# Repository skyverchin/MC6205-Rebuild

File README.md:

# MC6205-Rebuild
Restoration of soviet era plasma display

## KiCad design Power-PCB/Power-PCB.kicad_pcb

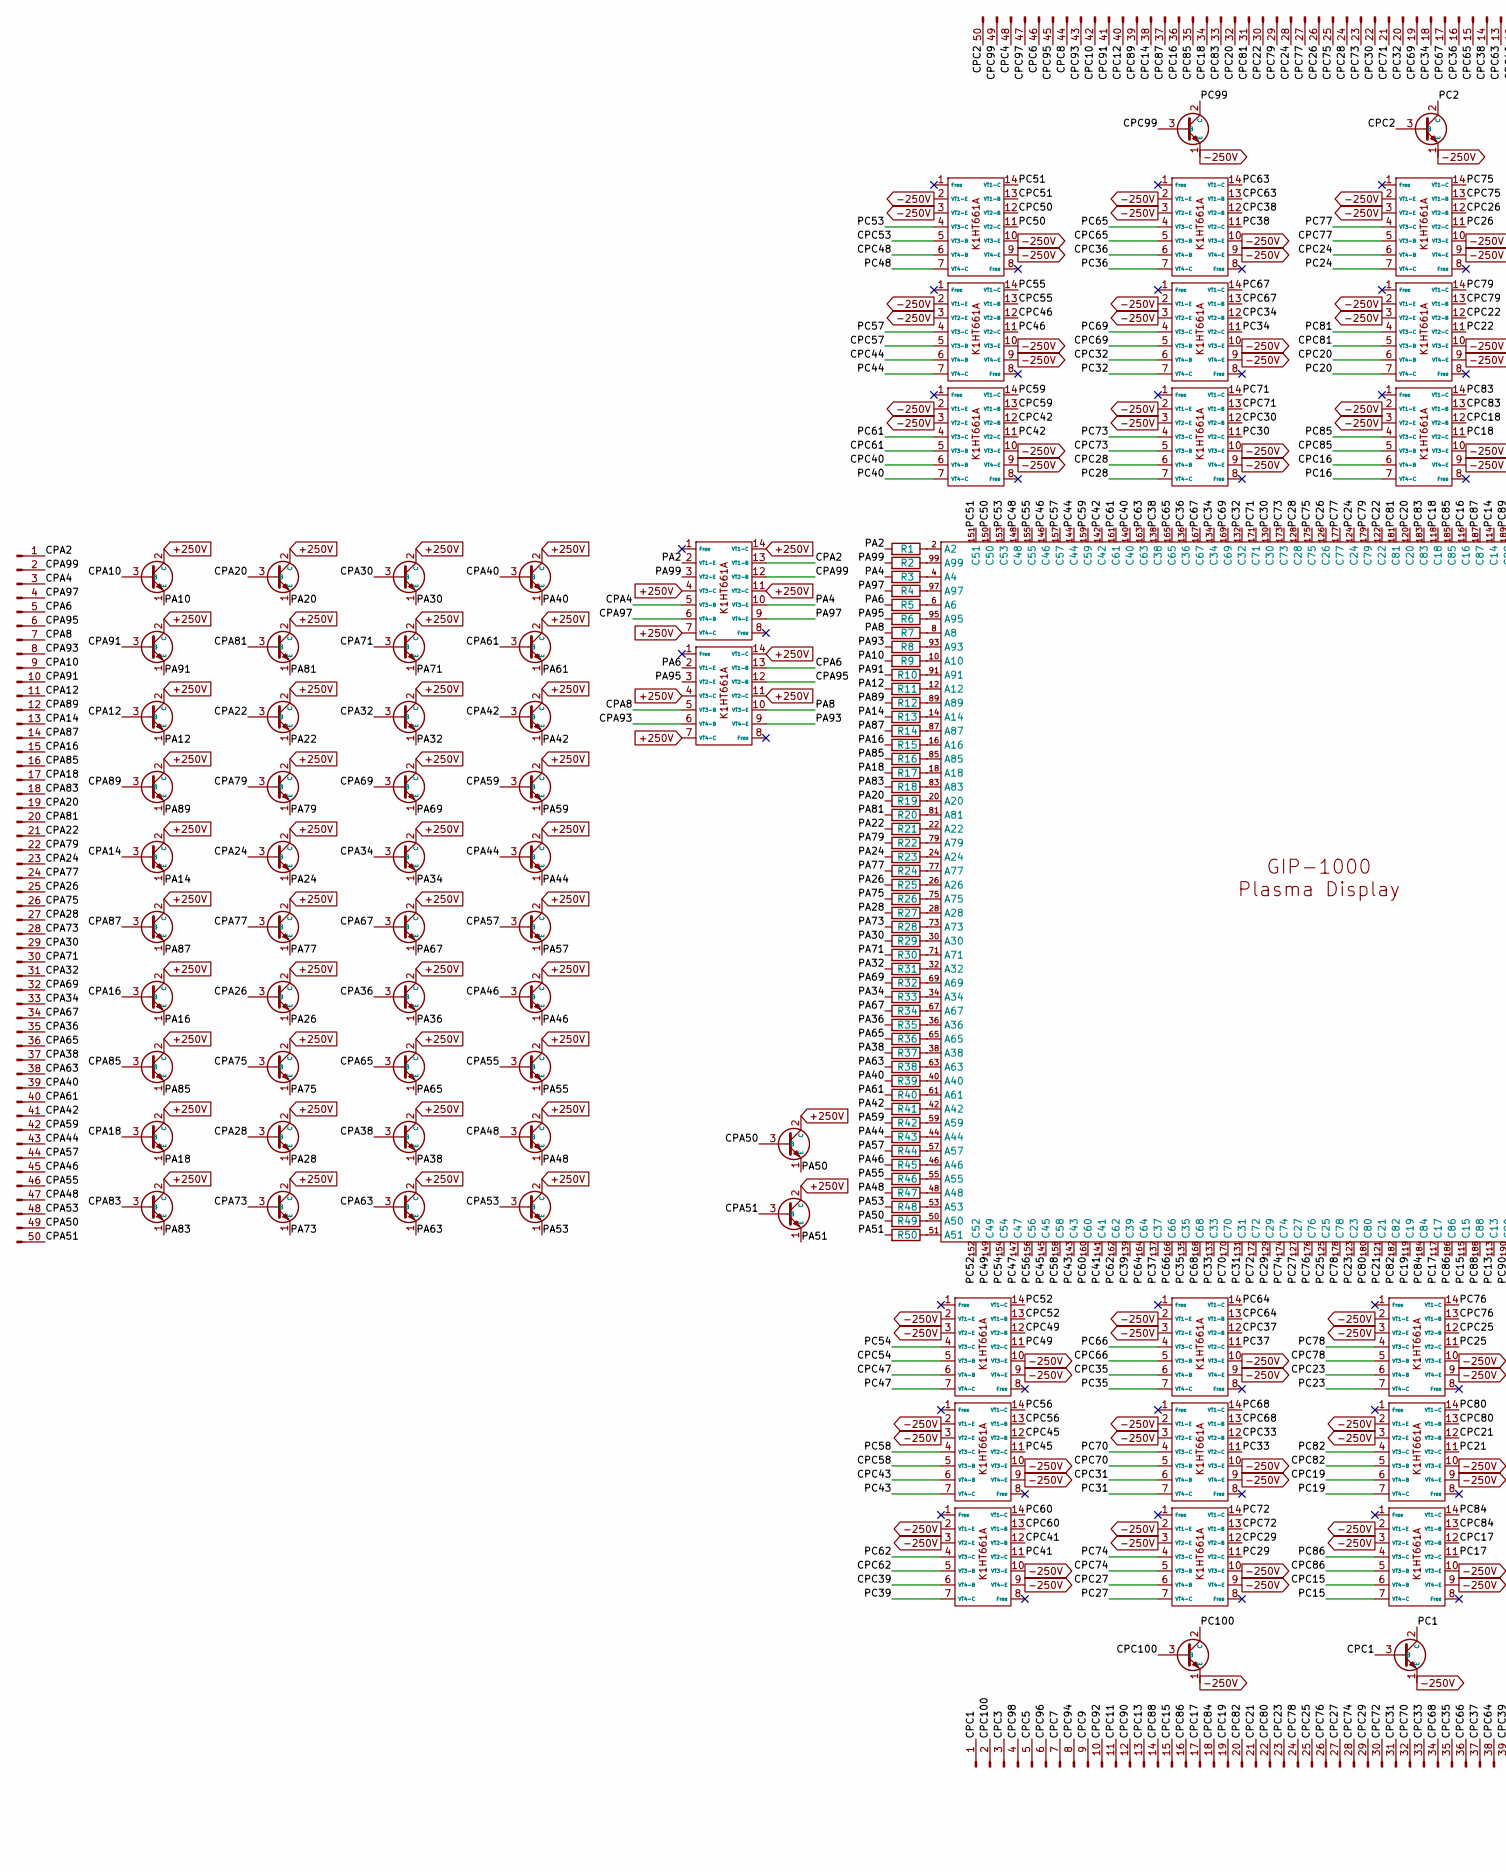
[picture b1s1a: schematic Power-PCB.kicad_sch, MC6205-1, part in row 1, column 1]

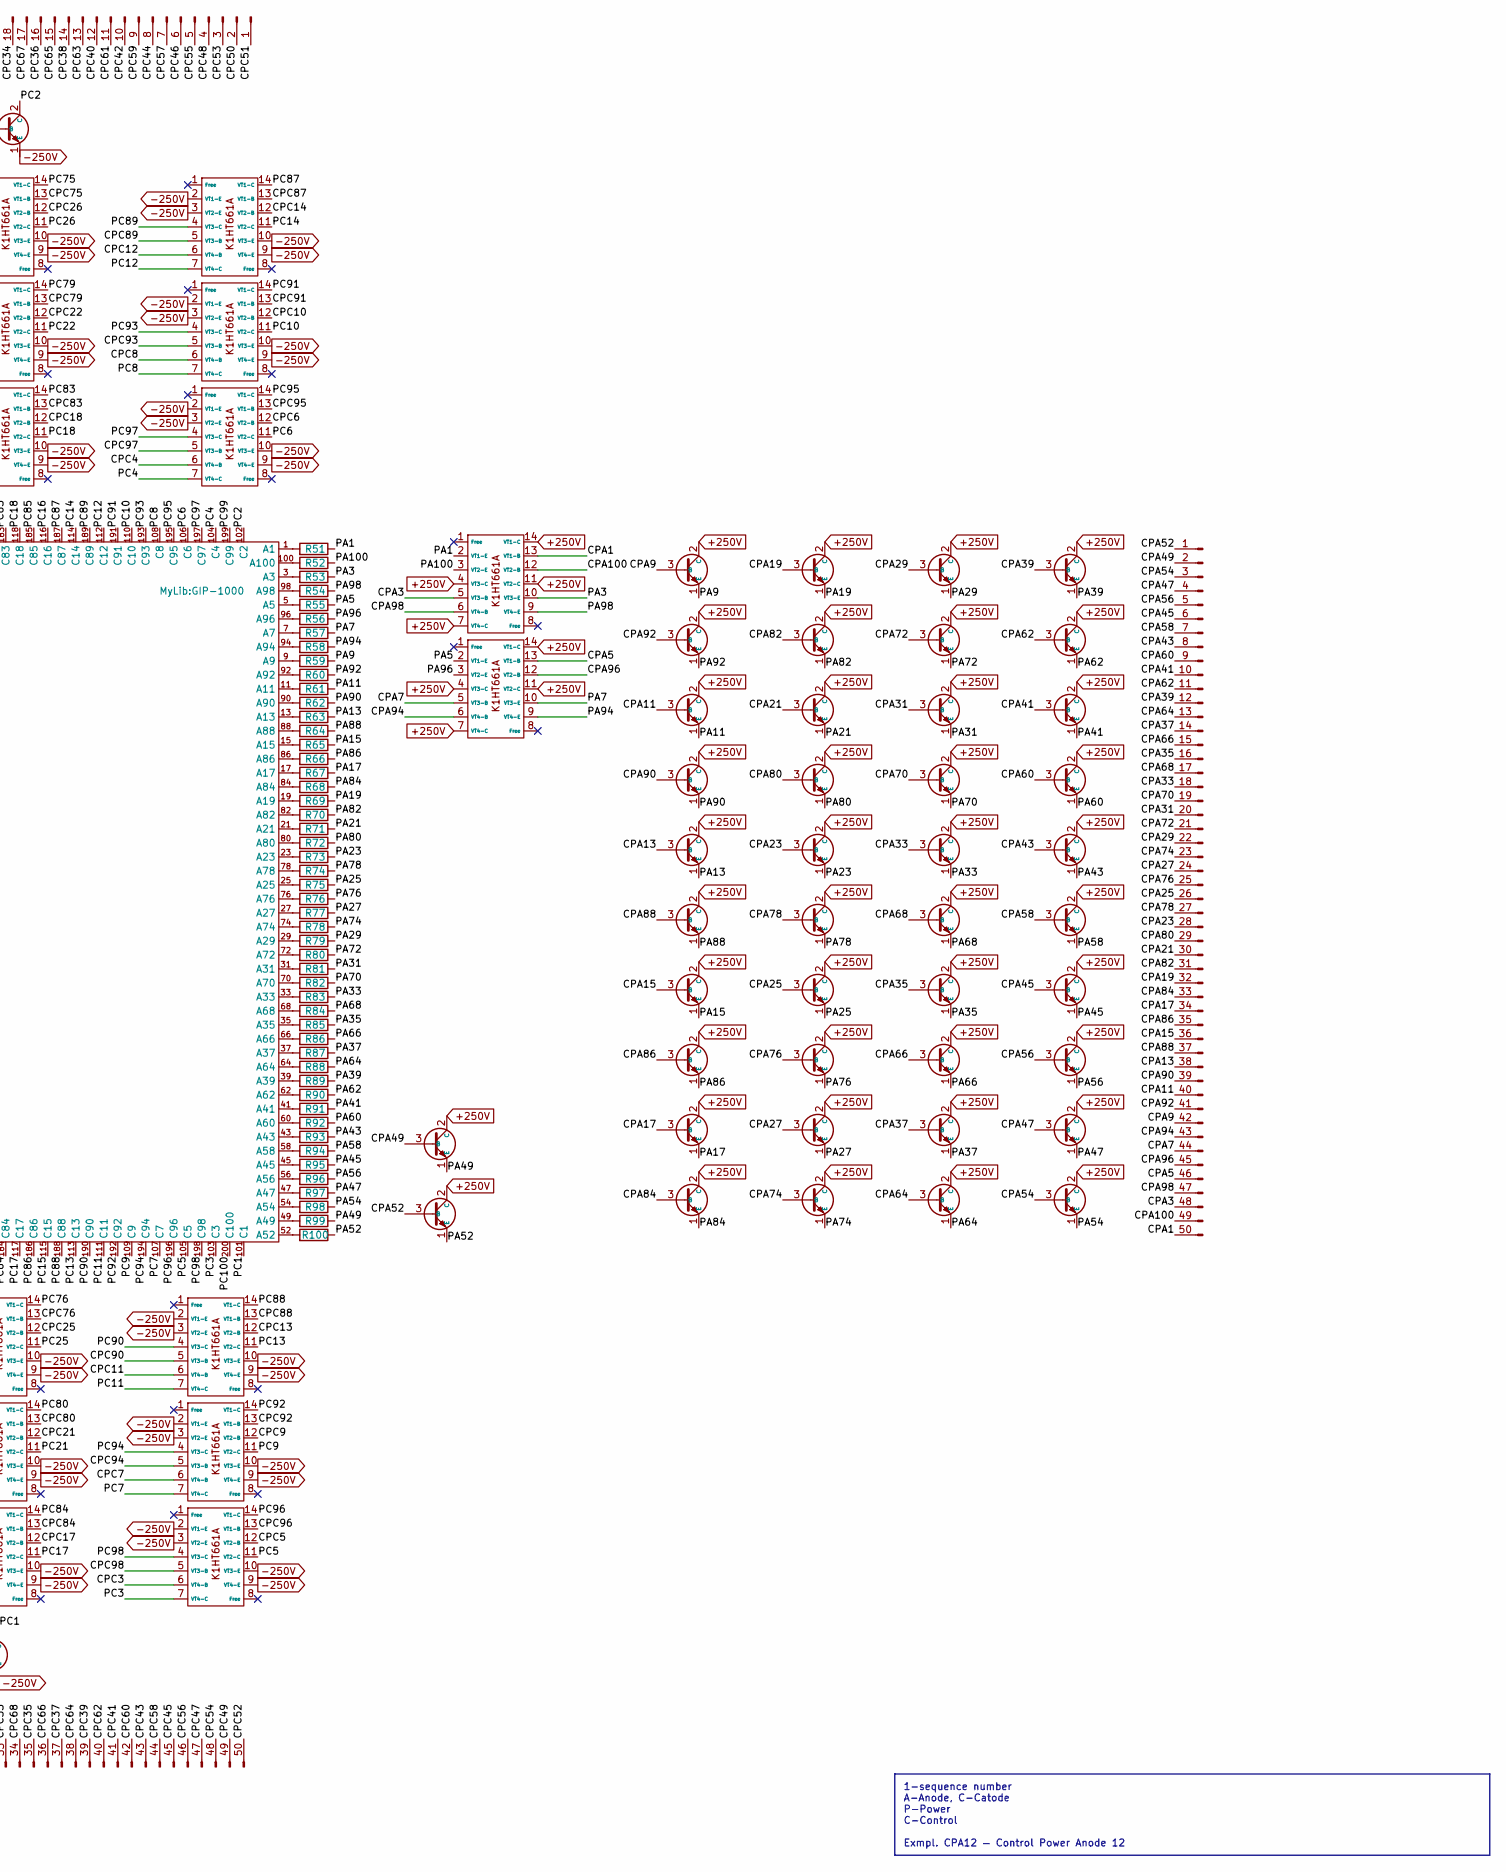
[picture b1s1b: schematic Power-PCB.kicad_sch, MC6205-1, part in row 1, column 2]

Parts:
J1, J2, J3, J4: Conn_01x50_Pin; Molex_54132-5033_1x50-1MP_P0.5mm_Horizontal
R1, R2, R3, R4, R5, R6, R7, R8, R9, R10, R11, R12, R13, R14, R15, R16, R17, R18, R19, R20, R21, R22, R23, R24, R25, R26, R27, R28, R29, R30, R31, R32, R33, R34, R35, R36, R37, R38, R39, R40, R41, R42, R43, R44, R45, R46, R47, R48, R49, R50, R51, R52, R53, R54, R55, R56, R57, R58, R59, R60, R61, R62, R63, R64, R65, R66, R67, R68, R69, R70, R71, R72, R73, R74, R75, R76, R77, R78, R79, R80, R81, R82, R83, R84, R85, R86, R87, R88, R89, R90, R91, R92, R93, R94, R95, R96, R97, R98, R99, R100: R_5K1; 5K1
U1, U2, U3, U4, U5, U6, U7, U8, U9, U10, U11, U12, U13, U14, U15, U16, U17, U18, U19, U20, U21, U22, U23, U24, U25, U26, U27, U28, U29, U30, U31, U32, U33, U34, U35, U36, U37, U38, U39, U40, U43, U44, U51, U52, U60, U67, U74, U75, U78, U79, U80, U81, U82, U83, U84, U85, U86, U87, U88, U89, U90, U91, U92, U93, U94, U95, U96, U97, U98, U99, U100, U101, U102, U103, U104, U105, U106, U107, U108, U109, U110, U111, U112, U113, U114, U115, U116, U117: BF422-FTPRNT
U41, U42, U45, U46, U47, U48, U49, U50, U53, U54, U55, U56, U57, U58, U61, U62, U63, U64, U65, U66, U68, U69, U70, U71, U72, U73, U76, U77: K1HT661A-FTPRNT
U59: GIP-1000

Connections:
+250V: U1.2 (C), U2.2 (C), U3.2 (C), U4.2 (C), U5.2 (C), U6.2 (C), U7.2 (C), U8.2 (C), U9.2 (C), U10.2 (C), U11.2 (C), U12.2 (C), U13.2 (C), U14.2 (C), U15.2 (C), U16.2 (C), U17.2 (C), U18.2 (C), U19.2 (C), U20.2 (C), U21.2 (C), U22.2 (C), U23.2 (C), U24.2 (C), U25.2 (C), U26.2 (C), U27.2 (C), U28.2 (C), U29.2 (C), U30.2 (C), U31.2 (C), U32.2 (C), U33.2 (C), U34.2 (C), U35.2 (C), U36.2 (C), U37.2 (C), U38.2 (C), U39.2 (C), U40.2 (C), U41.4 (VT3-C), U41.7 (VT4-C), U41.11 (VT2-C), U41.14 (VT1-C), U42.4 (VT3-C), U42.7 (VT4-C), U42.11 (VT2-C), U42.14 (VT1-C), U43.2 (C), U44.2 (C), U74.2 (C), U75.2 (C), U76.4 (VT3-C), U76.7 (VT4-C), U76.11 (VT2-C), U76.14 (VT1-C), U77.4 (VT3-C), U77.7 (VT4-C), U77.11 (VT2-C), U77.14 (VT1-C), U78.2 (C), U79.2 (C), U80.2 (C), U81.2 (C), U82.2 (C), U83.2 (C), U84.2 (C), U85.2 (C), U86.2 (C), U87.2 (C), U88.2 (C), U89.2 (C), U90.2 (C), U91.2 (C), U92.2 (C), U93.2 (C), U94.2 (C), U95.2 (C), U96.2 (C), U97.2 (C), U98.2 (C), U99.2 (C), U100.2 (C), U101.2 (C), U102.2 (C), U103.2 (C), U104.2 (C), U105.2 (C), U106.2 (C), U107.2 (C), U108.2 (C), U109.2 (C), U110.2 (C), U111.2 (C), U112.2 (C), U113.2 (C), U114.2 (C), U115.2 (C), U116.2 (C), U117.2 (C)
-250V: U45.2 (VT1-E), U45.3 (VT2-E), U45.9 (VT4-E), U45.10 (VT3-E), U46.2 (VT1-E), U46.3 (VT2-E), U46.9 (VT4-E), U46.10 (VT3-E), U47.2 (VT1-E), U47.3 (VT2-E), U47.9 (VT4-E), U47.10 (VT3-E), U48.2 (VT1-E), U48.3 (VT2-E), U48.9 (VT4-E), U48.10 (VT3-E), U49.2 (VT1-E), U49.3 (VT2-E), U49.9 (VT4-E), U49.10 (VT3-E), U50.2 (VT1-E), U50.3 (VT2-E), U50.9 (VT4-E), U50.10 (VT3-E), U51.1 (E), U52.1 (E), U53.2 (VT1-E), U53.3 (VT2-E), U53.9 (VT4-E), U53.10 (VT3-E), U54.2 (VT1-E), U54.3 (VT2-E), U54.9 (VT4-E), U54.10 (VT3-E), U55.2 (VT1-E), U55.3 (VT2-E), U55.9 (VT4-E), U55.10 (VT3-E), U56.2 (VT1-E), U56.3 (VT2-E), U56.9 (VT4-E), U56.10 (VT3-E), U57.2 (VT1-E), U57.3 (VT2-E), U57.9 (VT4-E), U57.10 (VT3-E), U58.2 (VT1-E), U58.3 (VT2-E), U58.9 (VT4-E), U58.10 (VT3-E), U60.1 (E), U61.2 (VT1-E), U61.3 (VT2-E), U61.9 (VT4-E), U61.10 (VT3-E), U62.2 (VT1-E), U62.3 (VT2-E), U62.9 (VT4-E), U62.10 (VT3-E), U63.2 (VT1-E), U63.3 (VT2-E), U63.9 (VT4-E), U63.10 (VT3-E), U64.2 (VT1-E), U64.3 (VT2-E), U64.9 (VT4-E), U64.10 (VT3-E), U65.2 (VT1-E), U65.3 (VT2-E), U65.9 (VT4-E), U65.10 (VT3-E), U66.2 (VT1-E), U66.3 (VT2-E), U66.9 (VT4-E), U66.10 (VT3-E), U67.1 (E), U68.2 (VT1-E), U68.3 (VT2-E), U68.9 (VT4-E), U68.10 (VT3-E), U69.2 (VT1-E), U69.3 (VT2-E), U69.9 (VT4-E), U69.10 (VT3-E), U70.2 (VT1-E), U70.3 (VT2-E), U70.9 (VT4-E), U70.10 (VT3-E), U71.2 (VT1-E), U71.3 (VT2-E), U71.9 (VT4-E), U71.10 (VT3-E), U72.2 (VT1-E), U72.3 (VT2-E), U72.9 (VT4-E), U72.10 (VT3-E), U73.2 (VT1-E), U73.3 (VT2-E), U73.9 (VT4-E), U73.10 (VT3-E)
/CPA1: J4.50, U76.13 (VT1-B)
/CPA3: J4.48, U76.5 (VT3-B)
/CPA5: J4.46, U77.13 (VT1-B)
/CPA7: J4.44, U77.5 (VT3-B)
/CPA9: J4.42, U78.3 (B)
/CPA11: J4.40, U80.3 (B)
/CPA13: J4.38, U82.3 (B)
/CPA15: J4.36, U84.3 (B)
/CPA17: J4.34, U86.3 (B)
/CPA19: J4.32, U88.3 (B)
/CPA21: J4.30, U90.3 (B)
/CPA23: J4.28, U92.3 (B)
/CPA25: J4.26, U94.3 (B)
/CPA27: J4.24, U96.3 (B)
/CPA29: J4.22, U98.3 (B)
/CPA31: J4.20, U100.3 (B)
/CPA33: J4.18, U102.3 (B)
/CPA35: J4.16, U104.3 (B)
/CPA37: J4.14, U106.3 (B)
/CPA39: J4.12, U108.3 (B)
/CPA41: J4.10, U110.3 (B)
/CPA43: J4.8, U112.3 (B)
/CPA45: J4.6, U114.3 (B)
/CPA47: J4.4, U116.3 (B)
/CPA49: J4.2, U74.3 (B)
/CPA52: J4.1, U75.3 (B)
/CPA54: J4.3, U117.3 (B)
/CPA56: J4.5, U115.3 (B)
/CPA58: J4.7, U113.3 (B)
/CPA60: J4.9, U111.3 (B)
/CPA62: J4.11, U109.3 (B)
/CPA64: J4.13, U107.3 (B)
/CPA66: J4.15, U105.3 (B)
/CPA68: J4.17, U103.3 (B)
/CPA70: J4.19, U101.3 (B)
/CPA72: J4.21, U99.3 (B)
/CPA74: J4.23, U97.3 (B)
/CPA76: J4.25, U95.3 (B)
/CPA78: J4.27, U93.3 (B)
/CPA80: J4.29, U91.3 (B)
/CPA82: J4.31, U89.3 (B)
/CPA84: J4.33, U87.3 (B)
/CPA86: J4.35, U85.3 (B)
/CPA88: J4.37, U83.3 (B)
/CPA90: J4.39, U81.3 (B)
/CPA92: J4.41, U79.3 (B)
/CPA94: J4.43, U77.6 (VT4-B)
/CPA96: J4.45, U77.12 (VT2-B)
/CPA98: J4.47, U76.6 (VT4-B)
/CPA100: J4.49, U76.12 (VT2-B)
/CPC1: J2.1, U60.3 (B)
/CPC2: J3.50, U67.3 (B)
/CPC3: J2.3, U70.6 (VT4-B)
/CPC4: J3.48, U73.6 (VT4-B)
/CPC5: J2.5, U70.12 (VT2-B)
/CPC6: J3.46, U73.12 (VT2-B)
/CPC7: J2.7, U69.6 (VT4-B)
/CPC8: J3.44, U72.6 (VT4-B)
/CPC9: J2.9, U69.12 (VT2-B)
/CPC10: J3.42, U72.12 (VT2-B)
/CPC11: J2.11, U68.6 (VT4-B)
/CPC12: J3.40, U71.6 (VT4-B)
/CPC13: J2.13, U68.12 (VT2-B)
/CPC14: J3.38, U71.12 (VT2-B)
/CPC15: J2.15, U63.6 (VT4-B)
/CPC16: J3.36, U66.6 (VT4-B)
/CPC17: J2.17, U63.12 (VT2-B)
/CPC18: J3.34, U66.12 (VT2-B)
/CPC19: J2.19, U62.6 (VT4-B)
/CPC20: J3.32, U65.6 (VT4-B)
/CPC21: J2.21, U62.12 (VT2-B)
/CPC22: J3.30, U65.12 (VT2-B)
/CPC23: J2.23, U61.6 (VT4-B)
/CPC24: J3.28, U64.6 (VT4-B)
/CPC25: J2.25, U61.12 (VT2-B)
/CPC26: J3.26, U64.12 (VT2-B)
/CPC27: J2.27, U58.6 (VT4-B)
/CPC28: J3.24, U55.6 (VT4-B)
/CPC29: J2.29, U58.12 (VT2-B)
/CPC30: J3.22, U55.12 (VT2-B)
/CPC31: J2.31, U57.6 (VT4-B)
/CPC32: J3.20, U54.6 (VT4-B)
/CPC33: J2.33, U57.12 (VT2-B)
/CPC34: J3.18, U54.12 (VT2-B)
/CPC35: J2.35, U56.6 (VT4-B)
/CPC36: J3.16, U53.6 (VT4-B)
/CPC37: J2.37, U56.12 (VT2-B)
/CPC38: J3.14, U53.12 (VT2-B)
/CPC39: J2.39, U50.6 (VT4-B)
/CPC40: J3.12, U47.6 (VT4-B)
/CPC41: J2.41, U50.12 (VT2-B)
/CPC42: J3.10, U47.12 (VT2-B)
/CPC43: J2.43, U49.6 (VT4-B)
/CPC44: J3.8, U46.6 (VT4-B)
/CPC45: J2.45, U49.12 (VT2-B)
/CPC46: J3.6, U46.12 (VT2-B)
/CPC47: J2.47, U48.6 (VT4-B)
/CPC48: J3.4, U45.6 (VT4-B)
/CPC49: J2.49, U48.12 (VT2-B)
/CPC50: J3.2, U45.12 (VT2-B)
/CPC51: J3.1, U45.13 (VT1-B)
/CPC52: J2.50, U48.13 (VT1-B)
/CPC53: J3.3, U45.5 (VT3-B)
/CPC54: J2.48, U48.5 (VT3-B)
/CPC55: J3.5, U46.13 (VT1-B)
/CPC56: J2.46, U49.13 (VT1-B)
/CPC57: J3.7, U46.5 (VT3-B)
/CPC58: J2.44, U49.5 (VT3-B)
/CPC59: J3.9, U47.13 (VT1-B)
/CPC60: J2.42, U50.13 (VT1-B)
/CPC61: J3.11, U47.5 (VT3-B)
/CPC62: J2.40, U50.5 (VT3-B)
/CPC63: J3.13, U53.13 (VT1-B)
/CPC64: J2.38, U56.13 (VT1-B)
/CPC65: J3.15, U53.5 (VT3-B)
/CPC66: J2.36, U56.5 (VT3-B)
/CPC67: J3.17, U54.13 (VT1-B)
/CPC68: J2.34, U57.13 (VT1-B)
/CPC69: J3.19, U54.5 (VT3-B)
/CPC70: J2.32, U57.5 (VT3-B)
/CPC71: J3.21, U55.13 (VT1-B)
/CPC72: J2.30, U58.13 (VT1-B)
/CPC73: J3.23, U55.5 (VT3-B)
/CPC74: J2.28, U58.5 (VT3-B)
/CPC75: J3.25, U64.13 (VT1-B)
/CPC76: J2.26, U61.13 (VT1-B)
/CPC77: J3.27, U64.5 (VT3-B)
/CPC78: J2.24, U61.5 (VT3-B)
/CPC79: J3.29, U65.13 (VT1-B)
/CPC80: J2.22, U62.13 (VT1-B)
/CPC81: J3.31, U65.5 (VT3-B)
/CPC82: J2.20, U62.5 (VT3-B)
/CPC83: J3.33, U66.13 (VT1-B)
/CPC84: J2.18, U63.13 (VT1-B)
/CPC85: J3.35, U66.5 (VT3-B)
/CPC86: J2.16, U63.5 (VT3-B)
/CPC87: J3.37, U71.13 (VT1-B)
/CPC88: J2.14, U68.13 (VT1-B)
/CPC89: J3.39, U71.5 (VT3-B)
/CPC90: J2.12, U68.5 (VT3-B)
/CPC91: J3.41, U72.13 (VT1-B)
/CPC92: J2.10, U69.13 (VT1-B)
/CPC93: J3.43, U72.5 (VT3-B)
/CPC94: J2.8, U69.5 (VT3-B)
/CPC95: J3.45, U73.13 (VT1-B)
/CPC96: J2.6, U70.13 (VT1-B)
/CPC97: J3.47, U73.5 (VT3-B)
/CPC98: J2.4, U70.5 (VT3-B)
/CPC99: J3.49, U51.3 (B)
/CPC100: J2.2, U52.3 (B)
/PA1: R51.2, U76.2 (VT1-E)
/PA2: R1.1, U41.2 (VT1-E)
/PA3: R53.2, U76.10 (VT3-E)
/PA4: R3.1, U41.10 (VT3-E)
/PA5: R55.2, U77.2 (VT1-E)
/PA6: R5.1, U42.2 (VT1-E)
/PA7: R57.2, U77.10 (VT3-E)
/PA8: R7.1, U42.10 (VT3-E)
/PA9: R59.2, U78.1 (E)
/PA10: R9.1, U1.1 (E)
/PA11: R61.2, U80.1 (E)
/PA12: R11.1, U3.1 (E)
/PA13: R63.2, U82.1 (E)
/PA14: R13.1, U5.1 (E)
/PA15: R65.2, U84.1 (E)
/PA16: R15.1, U7.1 (E)
/PA17: R67.2, U86.1 (E)
/PA18: R17.1, U9.1 (E)
/PA19: R69.2, U88.1 (E)
/PA20: R19.1, U11.1 (E)
/PA21: R71.2, U90.1 (E)
/PA22: R21.1, U13.1 (E)
/PA23: R73.2, U92.1 (E)
/PA24: R23.1, U15.1 (E)
/PA25: R75.2, U94.1 (E)
/PA26: R25.1, U17.1 (E)
/PA27: R77.2, U96.1 (E)
/PA28: R27.1, U19.1 (E)
/PA29: R79.2, U98.1 (E)
/PA30: R29.1, U21.1 (E)
/PA31: R81.2, U100.1 (E)
/PA32: R31.1, U23.1 (E)
/PA33: R83.2, U102.1 (E)
/PA34: R33.1, U25.1 (E)
/PA35: R85.2, U104.1 (E)
/PA36: R35.1, U27.1 (E)
/PA37: R87.2, U106.1 (E)
/PA38: R37.1, U29.1 (E)
/PA39: R89.2, U108.1 (E)
/PA40: R39.1, U31.1 (E)
/PA41: R91.2, U110.1 (E)
/PA42: R41.1, U33.1 (E)
/PA43: R93.2, U112.1 (E)
/PA44: R43.1, U35.1 (E)
/PA45: R95.2, U114.1 (E)
/PA46: R45.1, U37.1 (E)
/PA47: R97.2, U116.1 (E)
/PA48: R47.1, U39.1 (E)
/PA49: R99.2, U74.1 (E)
/PA50: R49.1, U43.1 (E)
/PA51: R50.1, U44.1 (E)
/PA52: R100.2, U75.1 (E)
/PA53: R48.1, U40.1 (E)
/PA54: R98.2, U117.1 (E)
/PA55: R46.1, U38.1 (E)
/PA56: R96.2, U115.1 (E)
/PA57: R44.1, U36.1 (E)
/PA58: R94.2, U113.1 (E)
/PA59: R42.1, U34.1 (E)
/PA60: R92.2, U111.1 (E)
/PA61: R40.1, U32.1 (E)
/PA62: R90.2, U109.1 (E)
/PA63: R38.1, U30.1 (E)
/PA64: R88.2, U107.1 (E)
/PA65: R36.1, U28.1 (E)
/PA66: R86.2, U105.1 (E)
/PA67: R34.1, U26.1 (E)
/PA68: R84.2, U103.1 (E)
/PA69: R32.1, U24.1 (E)
/PA70: R82.2, U101.1 (E)
/PA71: R30.1, U22.1 (E)
/PA72: R80.2, U99.1 (E)
/PA73: R28.1, U20.1 (E)
/PA74: R78.2, U97.1 (E)
/PA75: R26.1, U18.1 (E)
/PA76: R76.2, U95.1 (E)
/PA77: R24.1, U16.1 (E)
/PA78: R74.2, U93.1 (E)
/PA79: R22.1, U14.1 (E)
/PA80: R72.2, U91.1 (E)
/PA81: R20.1, U12.1 (E)
/PA82: R70.2, U89.1 (E)
/PA83: R18.1, U10.1 (E)
/PA84: R68.2, U87.1 (E)
/PA85: R16.1, U8.1 (E)
/PA86: R66.2, U85.1 (E)
/PA87: R14.1, U6.1 (E)
/PA88: R64.2, U83.1 (E)
/PA89: R12.1, U4.1 (E)
/PA90: R62.2, U81.1 (E)
/PA91: R10.1, U2.1 (E)
/PA92: R60.2, U79.1 (E)
/PA93: R8.1, U42.9 (VT4-E)
/PA94: R58.2, U77.9 (VT4-E)
/PA95: R6.1, U42.3 (VT2-E)
/PA96: R56.2, U77.3 (VT2-E)
/PA97: R4.1, U41.9 (VT4-E)
/PA98: R54.2, U76.9 (VT4-E)
/PA99: R2.1, U41.3 (VT2-E)
/PA100: R52.2, U76.3 (VT2-E)
/PC1: U59.101 (C1), U60.2 (C)
/PC2: U59.102 (C2), U67.2 (C)
/PC3: U59.103 (C3), U70.7 (VT4-C)
/PC4: U59.104 (C4), U73.7 (VT4-C)
/PC5: U59.105 (C5), U70.11 (VT2-C)
/PC6: U59.106 (C6), U73.11 (VT2-C)
/PC7: U59.107 (C7), U69.7 (VT4-C)
/PC8: U59.108 (C8), U72.7 (VT4-C)
/PC9: U59.109 (C9), U69.11 (VT2-C)
/PC10: U59.110 (C10), U72.11 (VT2-C)
/PC11: U59.111 (C11), U68.7 (VT4-C)
/PC12: U59.112 (C12), U71.7 (VT4-C)
/PC13: U59.113 (C13), U68.11 (VT2-C)
/PC14: U59.114 (C14), U71.11 (VT2-C)
/PC15: U59.115 (C15), U63.7 (VT4-C)
/PC16: U59.116 (C16), U66.7 (VT4-C)
/PC17: U59.117 (C17), U63.11 (VT2-C)
/PC18: U59.118 (C18), U66.11 (VT2-C)
/PC19: U59.119 (C19), U62.7 (VT4-C)
/PC20: U59.120 (C20), U65.7 (VT4-C)
/PC21: U59.121 (C21), U62.11 (VT2-C)
/PC22: U59.122 (C22), U65.11 (VT2-C)
/PC23: U59.123 (C23), U61.7 (VT4-C)
/PC24: U59.124 (C24), U64.7 (VT4-C)
/PC25: U59.125 (C25), U61.11 (VT2-C)
/PC26: U59.126 (C26), U64.11 (VT2-C)
/PC27: U58.7 (VT4-C), U59.127 (C27)
/PC28: U55.7 (VT4-C), U59.128 (C28)
/PC29: U58.11 (VT2-C), U59.129 (C29)
/PC30: U55.11 (VT2-C), U59.130 (C30)
/PC31: U57.7 (VT4-C), U59.131 (C31)
/PC32: U54.7 (VT4-C), U59.132 (C32)
/PC33: U57.11 (VT2-C), U59.133 (C33)
/PC34: U54.11 (VT2-C), U59.134 (C34)
/PC35: U56.7 (VT4-C), U59.135 (C35)
/PC36: U53.7 (VT4-C), U59.136 (C36)
/PC37: U56.11 (VT2-C), U59.137 (C37)
/PC38: U53.11 (VT2-C), U59.138 (C38)
/PC39: U50.7 (VT4-C), U59.139 (C39)
/PC40: U47.7 (VT4-C), U59.140 (C40)
/PC41: U50.11 (VT2-C), U59.141 (C41)
/PC42: U47.11 (VT2-C), U59.142 (C42)
/PC43: U49.7 (VT4-C), U59.143 (C43)
/PC44: U46.7 (VT4-C), U59.144 (C44)
/PC45: U49.11 (VT2-C), U59.145 (C45)
/PC46: U46.11 (VT2-C), U59.146 (C46)
/PC47: U48.7 (VT4-C), U59.147 (C47)
/PC48: U45.7 (VT4-C), U59.148 (C48)
/PC49: U48.11 (VT2-C), U59.149 (C49)
/PC50: U45.11 (VT2-C), U59.150 (C50)
/PC51: U45.14 (VT1-C), U59.151 (C51)
/PC52: U48.14 (VT1-C), U59.152 (C52)
/PC53: U45.4 (VT3-C), U59.153 (C53)
/PC54: U48.4 (VT3-C), U59.154 (C54)
/PC55: U46.14 (VT1-C), U59.155 (C55)
/PC56: U49.14 (VT1-C), U59.156 (C56)
/PC57: U46.4 (VT3-C), U59.157 (C57)
/PC58: U49.4 (VT3-C), U59.158 (C58)
/PC59: U47.14 (VT1-C), U59.159 (C59)
/PC60: U50.14 (VT1-C), U59.160 (C60)
/PC61: U47.4 (VT3-C), U59.161 (C61)
/PC62: U50.4 (VT3-C), U59.162 (C62)
/PC63: U53.14 (VT1-C), U59.163 (C63)
/PC64: U56.14 (VT1-C), U59.164 (C64)
/PC65: U53.4 (VT3-C), U59.165 (C65)
/PC66: U56.4 (VT3-C), U59.166 (C66)
/PC67: U54.14 (VT1-C), U59.167 (C67)
/PC68: U57.14 (VT1-C), U59.168 (C68)
/PC69: U54.4 (VT3-C), U59.169 (C69)
/PC70: U57.4 (VT3-C), U59.170 (C70)
/PC71: U55.14 (VT1-C), U59.171 (C71)
/PC72: U58.14 (VT1-C), U59.172 (C72)
/PC73: U55.4 (VT3-C), U59.173 (C73)
/PC74: U58.4 (VT3-C), U59.174 (C74)
/PC75: U59.175 (C75), U64.14 (VT1-C)
/PC76: U59.176 (C76), U61.14 (VT1-C)
/PC77: U59.177 (C77), U64.4 (VT3-C)
/PC78: U59.178 (C78), U61.4 (VT3-C)
/PC79: U59.179 (C79), U65.14 (VT1-C)
/PC80: U59.180 (C80), U62.14 (VT1-C)
/PC81: U59.181 (C81), U65.4 (VT3-C)
/PC82: U59.182 (C82), U62.4 (VT3-C)
/PC83: U59.183 (C83), U66.14 (VT1-C)
/PC84: U59.184 (C84), U63.14 (VT1-C)
/PC85: U59.185 (C85), U66.4 (VT3-C)
/PC86: U59.186 (C86), U63.4 (VT3-C)
/PC87: U59.187 (C87), U71.14 (VT1-C)
/PC88: U59.188 (C88), U68.14 (VT1-C)
/PC89: U59.189 (C89), U71.4 (VT3-C)
/PC90: U59.190 (C90), U68.4 (VT3-C)
/PC91: U59.191 (C91), U72.14 (VT1-C)
/PC92: U59.192 (C92), U69.14 (VT1-C)
/PC93: U59.193 (C93), U72.4 (VT3-C)
/PC94: U59.194 (C94), U69.4 (VT3-C)
/PC95: U59.195 (C95), U73.14 (VT1-C)
/PC96: U59.196 (C96), U70.14 (VT1-C)
/PC97: U59.197 (C97), U73.4 (VT3-C)
/PC98: U59.198 (C98), U70.4 (VT3-C)
/PC99: U51.2 (C), U59.199 (C99)
/PC100: U52.2 (C), U59.200 (C100)
/СPA2: J1.1, U41.13 (VT1-B)
/СPA4: J1.3, U41.5 (VT3-B)
/СPA6: J1.5, U42.13 (VT1-B)
/СPA8: J1.7, U42.5 (VT3-B)
/СPA10: J1.9, U1.3 (B)
/СPA12: J1.11, U3.3 (B)
/СPA14: J1.13, U5.3 (B)
/СPA16: J1.15, U7.3 (B)
/СPA18: J1.17, U9.3 (B)
/СPA20: J1.19, U11.3 (B)
/СPA22: J1.21, U13.3 (B)
/СPA24: J1.23, U15.3 (B)
/СPA26: J1.25, U17.3 (B)
/СPA28: J1.27, U19.3 (B)
/СPA30: J1.29, U21.3 (B)
/СPA32: J1.31, U23.3 (B)
/СPA34: J1.33, U25.3 (B)
/СPA36: J1.35, U27.3 (B)
/СPA38: J1.37, U29.3 (B)
/СPA40: J1.39, U31.3 (B)
/СPA42: J1.41, U33.3 (B)
/СPA44: J1.43, U35.3 (B)
/СPA46: J1.45, U37.3 (B)
/СPA48: J1.47, U39.3 (B)
/СPA50: J1.49, U43.3 (B)
/СPA51: J1.50, U44.3 (B)
/СPA53: J1.48, U40.3 (B)
/СPA55: J1.46, U38.3 (B)
/СPA57: J1.44, U36.3 (B)
/СPA59: J1.42, U34.3 (B)
/СPA61: J1.40, U32.3 (B)
/СPA63: J1.38, U30.3 (B)
/СPA65: J1.36, U28.3 (B)
/СPA67: J1.34, U26.3 (B)
/СPA69: J1.32, U24.3 (B)
/СPA71: J1.30, U22.3 (B)
/СPA73: J1.28, U20.3 (B)
/СPA75: J1.26, U18.3 (B)
/СPA77: J1.24, U16.3 (B)
/СPA79: J1.22, U14.3 (B)
/СPA81: J1.20, U12.3 (B)
/СPA83: J1.18, U10.3 (B)
/СPA85: J1.16, U8.3 (B)
/СPA87: J1.14, U6.3 (B)
/СPA89: J1.12, U4.3 (B)
/СPA91: J1.10, U2.3 (B)
/СPA93: J1.8, U42.6 (VT4-B)
/СPA95: J1.6, U42.12 (VT2-B)
/СPA97: J1.4, U41.6 (VT4-B)
/СPA99: J1.2, U41.12 (VT2-B)
unnamed: R51.1, U59.1 (A1)
unnamed: R1.2, U59.2 (A2)
unnamed: R53.1, U59.3 (A3)
unnamed: R3.2, U59.4 (A4)
unnamed: R55.1, U59.5 (A5)
unnamed: R5.2, U59.6 (A6)
unnamed: R57.1, U59.7 (A7)
unnamed: R7.2, U59.8 (A8)
unnamed: R59.1, U59.9 (A9)
unnamed: R9.2, U59.10 (A10)
unnamed: R61.1, U59.11 (A11)
unnamed: R11.2, U59.12 (A12)
unnamed: R63.1, U59.13 (A13)
unnamed: R13.2, U59.14 (A14)
unnamed: R65.1, U59.15 (A15)
unnamed: R15.2, U59.16 (A16)
unnamed: R67.1, U59.17 (A17)
unnamed: R17.2, U59.18 (A18)
unnamed: R69.1, U59.19 (A19)
unnamed: R19.2, U59.20 (A20)
unnamed: R71.1, U59.21 (A21)
unnamed: R21.2, U59.22 (A22)
unnamed: R73.1, U59.23 (A23)
unnamed: R23.2, U59.24 (A24)
unnamed: R75.1, U59.25 (A25)
unnamed: R25.2, U59.26 (A26)
unnamed: R77.1, U59.27 (A27)
unnamed: R27.2, U59.28 (A28)
unnamed: R79.1, U59.29 (A29)
unnamed: R29.2, U59.30 (A30)
unnamed: R81.1, U59.31 (A31)
unnamed: R31.2, U59.32 (A32)
unnamed: R83.1, U59.33 (A33)
unnamed: R33.2, U59.34 (A34)
unnamed: R85.1, U59.35 (A35)
unnamed: R35.2, U59.36 (A36)
unnamed: R87.1, U59.37 (A37)
unnamed: R37.2, U59.38 (A38)
unnamed: R89.1, U59.39 (A39)
unnamed: R39.2, U59.40 (A40)
unnamed: R91.1, U59.41 (A41)
unnamed: R41.2, U59.42 (A42)
unnamed: R93.1, U59.43 (A43)
unnamed: R43.2, U59.44 (A44)
unnamed: R95.1, U59.45 (A45)
unnamed: R45.2, U59.46 (A46)
unnamed: R97.1, U59.47 (A47)
unnamed: R47.2, U59.48 (A48)
unnamed: R99.1, U59.49 (A49)
unnamed: R49.2, U59.50 (A50)
unnamed: R50.2, U59.51 (A51)
unnamed: R100.1, U59.52 (A52)
unnamed: R48.2, U59.53 (A53)
unnamed: R98.1, U59.54 (A54)
unnamed: R46.2, U59.55 (A55)
unnamed: R96.1, U59.56 (A56)
unnamed: R44.2, U59.57 (A57)
unnamed: R94.1, U59.58 (A58)
unnamed: R42.2, U59.59 (A59)
unnamed: R92.1, U59.60 (A60)
unnamed: R40.2, U59.61 (A61)
unnamed: R90.1, U59.62 (A62)
unnamed: R38.2, U59.63 (A63)
unnamed: R88.1, U59.64 (A64)
unnamed: R36.2, U59.65 (A65)
unnamed: R86.1, U59.66 (A66)
unnamed: R34.2, U59.67 (A67)
unnamed: R84.1, U59.68 (A68)
unnamed: R32.2, U59.69 (A69)
unnamed: R82.1, U59.70 (A70)
unnamed: R30.2, U59.71 (A71)
unnamed: R80.1, U59.72 (A72)
unnamed: R28.2, U59.73 (A73)
unnamed: R78.1, U59.74 (A74)
unnamed: R26.2, U59.75 (A75)
unnamed: R76.1, U59.76 (A76)
unnamed: R24.2, U59.77 (A77)
unnamed: R74.1, U59.78 (A78)
unnamed: R22.2, U59.79 (A79)
unnamed: R72.1, U59.80 (A80)
unnamed: R20.2, U59.81 (A81)
unnamed: R70.1, U59.82 (A82)
unnamed: R18.2, U59.83 (A83)
unnamed: R68.1, U59.84 (A84)
unnamed: R16.2, U59.85 (A85)
unnamed: R66.1, U59.86 (A86)
unnamed: R14.2, U59.87 (A87)
unnamed: R64.1, U59.88 (A88)
unnamed: R12.2, U59.89 (A89)
unnamed: R62.1, U59.90 (A90)
unnamed: R10.2, U59.91 (A91)
unnamed: R60.1, U59.92 (A92)
unnamed: R8.2, U59.93 (A93)
unnamed: R58.1, U59.94 (A94)
unnamed: R6.2, U59.95 (A95)
unnamed: R56.1, U59.96 (A96)
unnamed: R4.2, U59.97 (A97)
unnamed: R54.1, U59.98 (A98)
unnamed: R2.2, U59.99 (A99)
unnamed: R52.1, U59.100 (A100)

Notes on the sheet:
1-sequence number A-Anode, C-Catode P-Power C-Control Exmpl. CPA12 — Control Power Anode 12

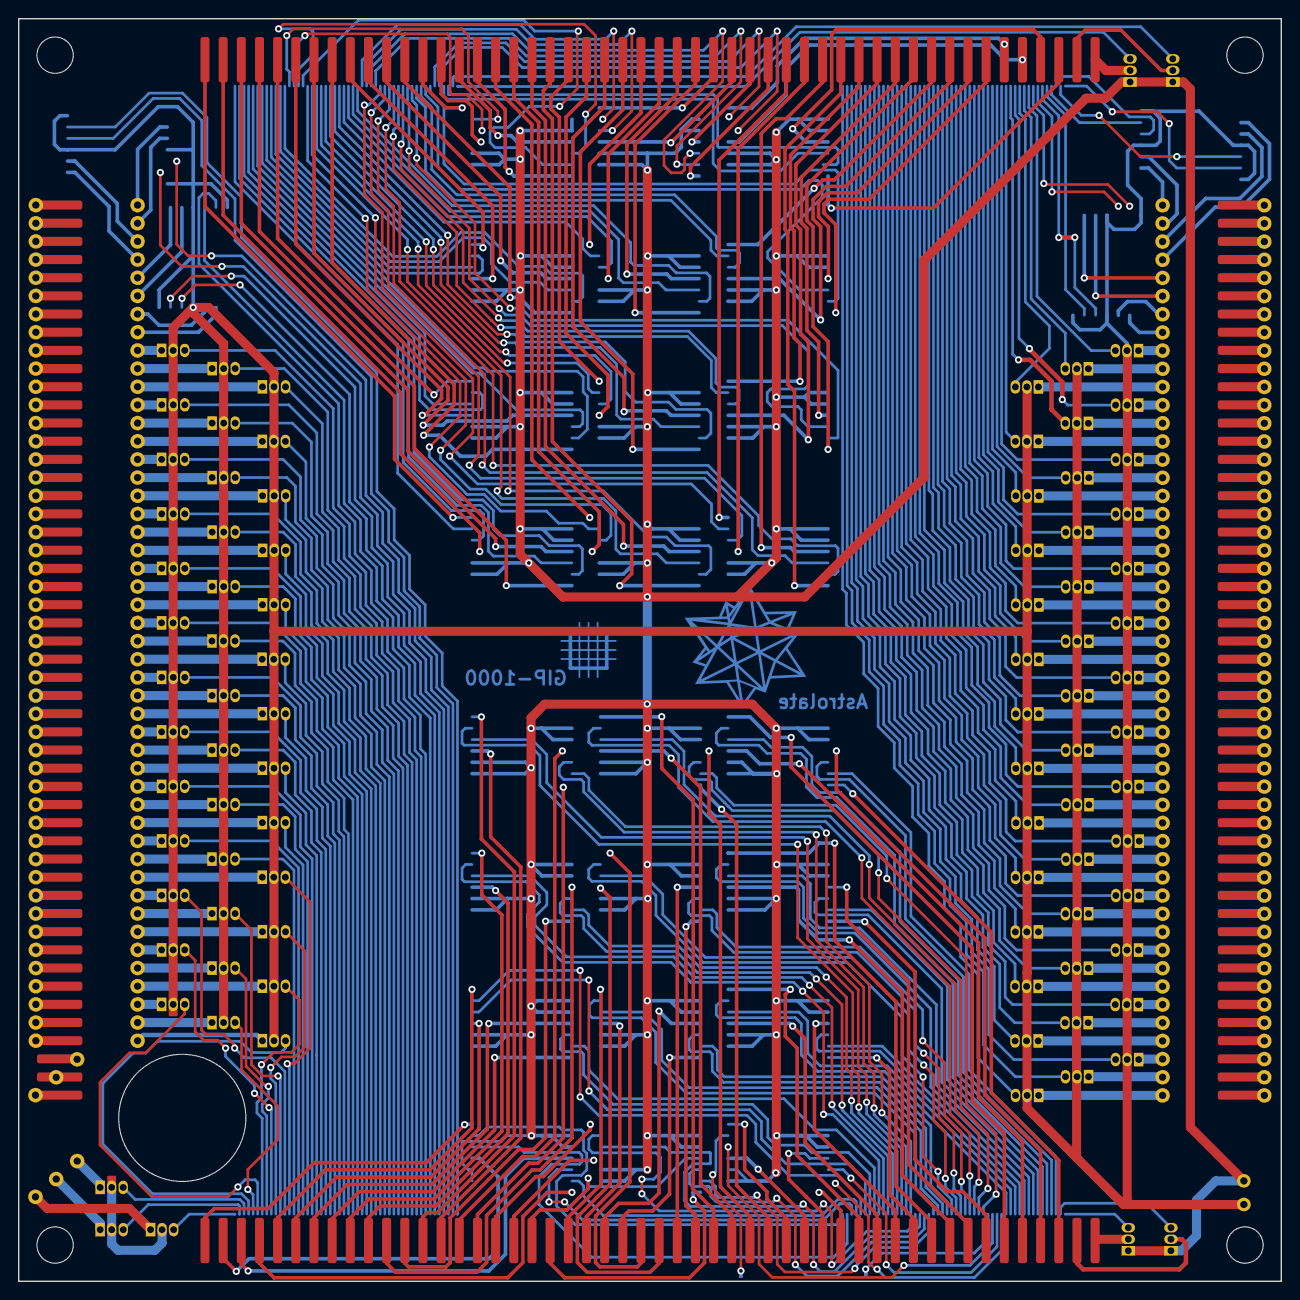
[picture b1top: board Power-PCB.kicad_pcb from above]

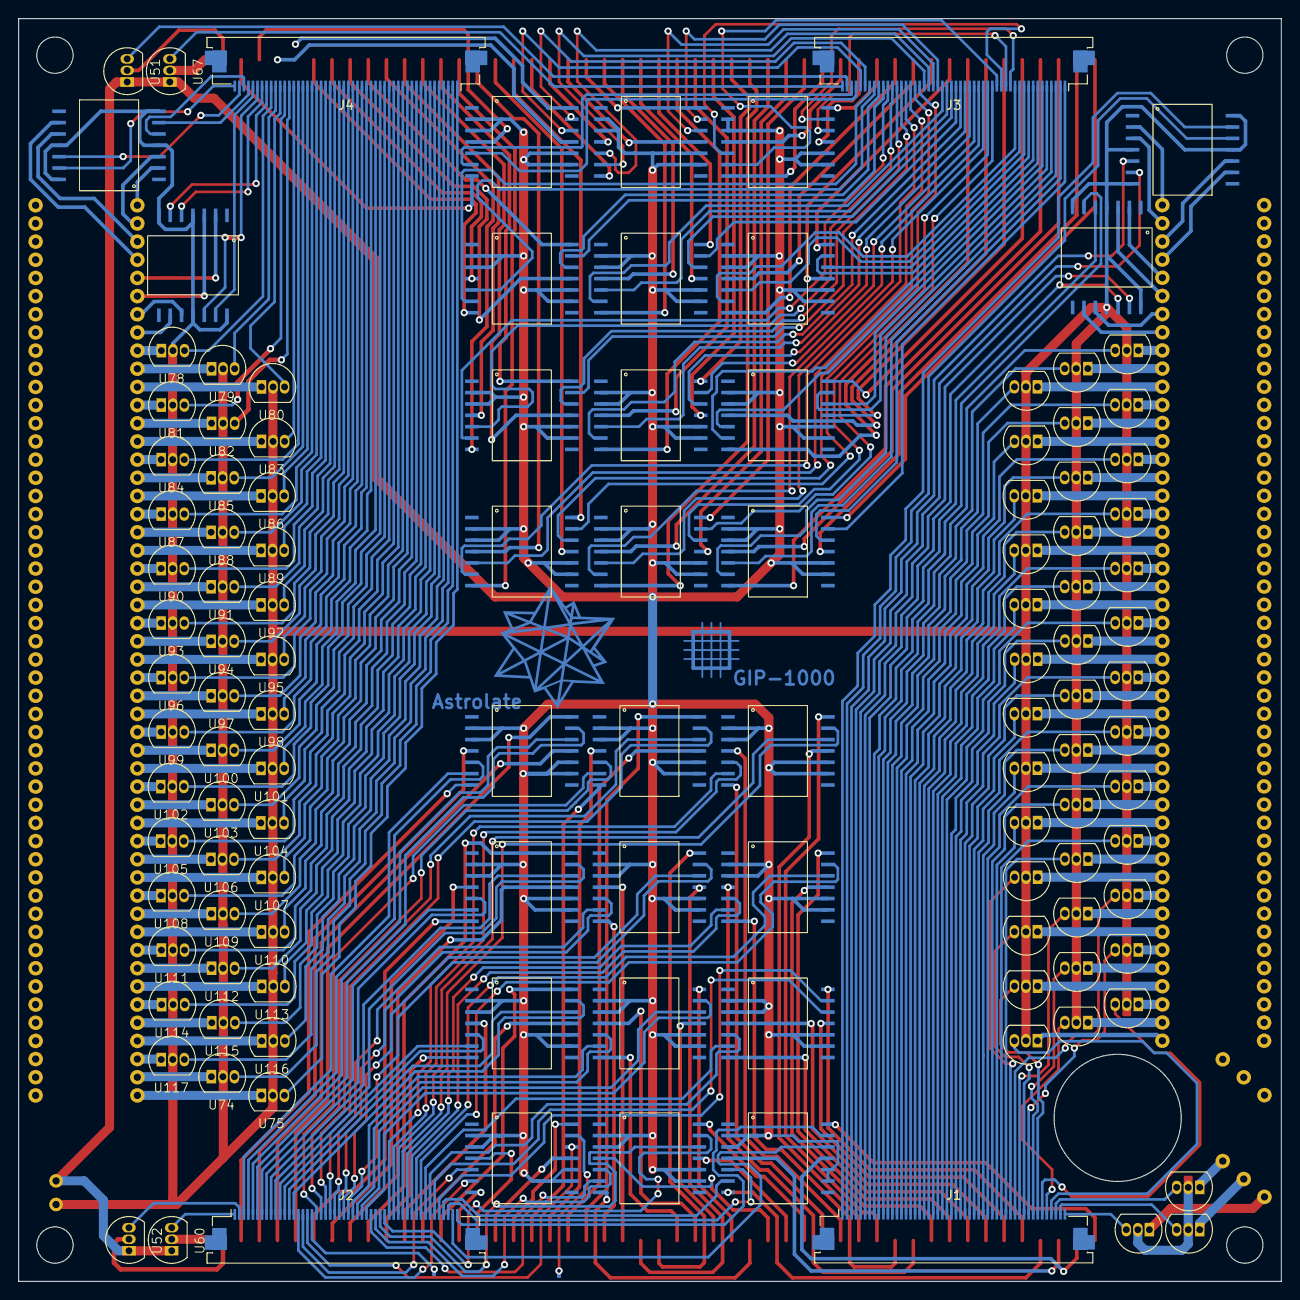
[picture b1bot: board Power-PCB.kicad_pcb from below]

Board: 2 copper layers, 139.0 x 139.0 mm, 221 parts (120 on the bottom side), 502 nets.
